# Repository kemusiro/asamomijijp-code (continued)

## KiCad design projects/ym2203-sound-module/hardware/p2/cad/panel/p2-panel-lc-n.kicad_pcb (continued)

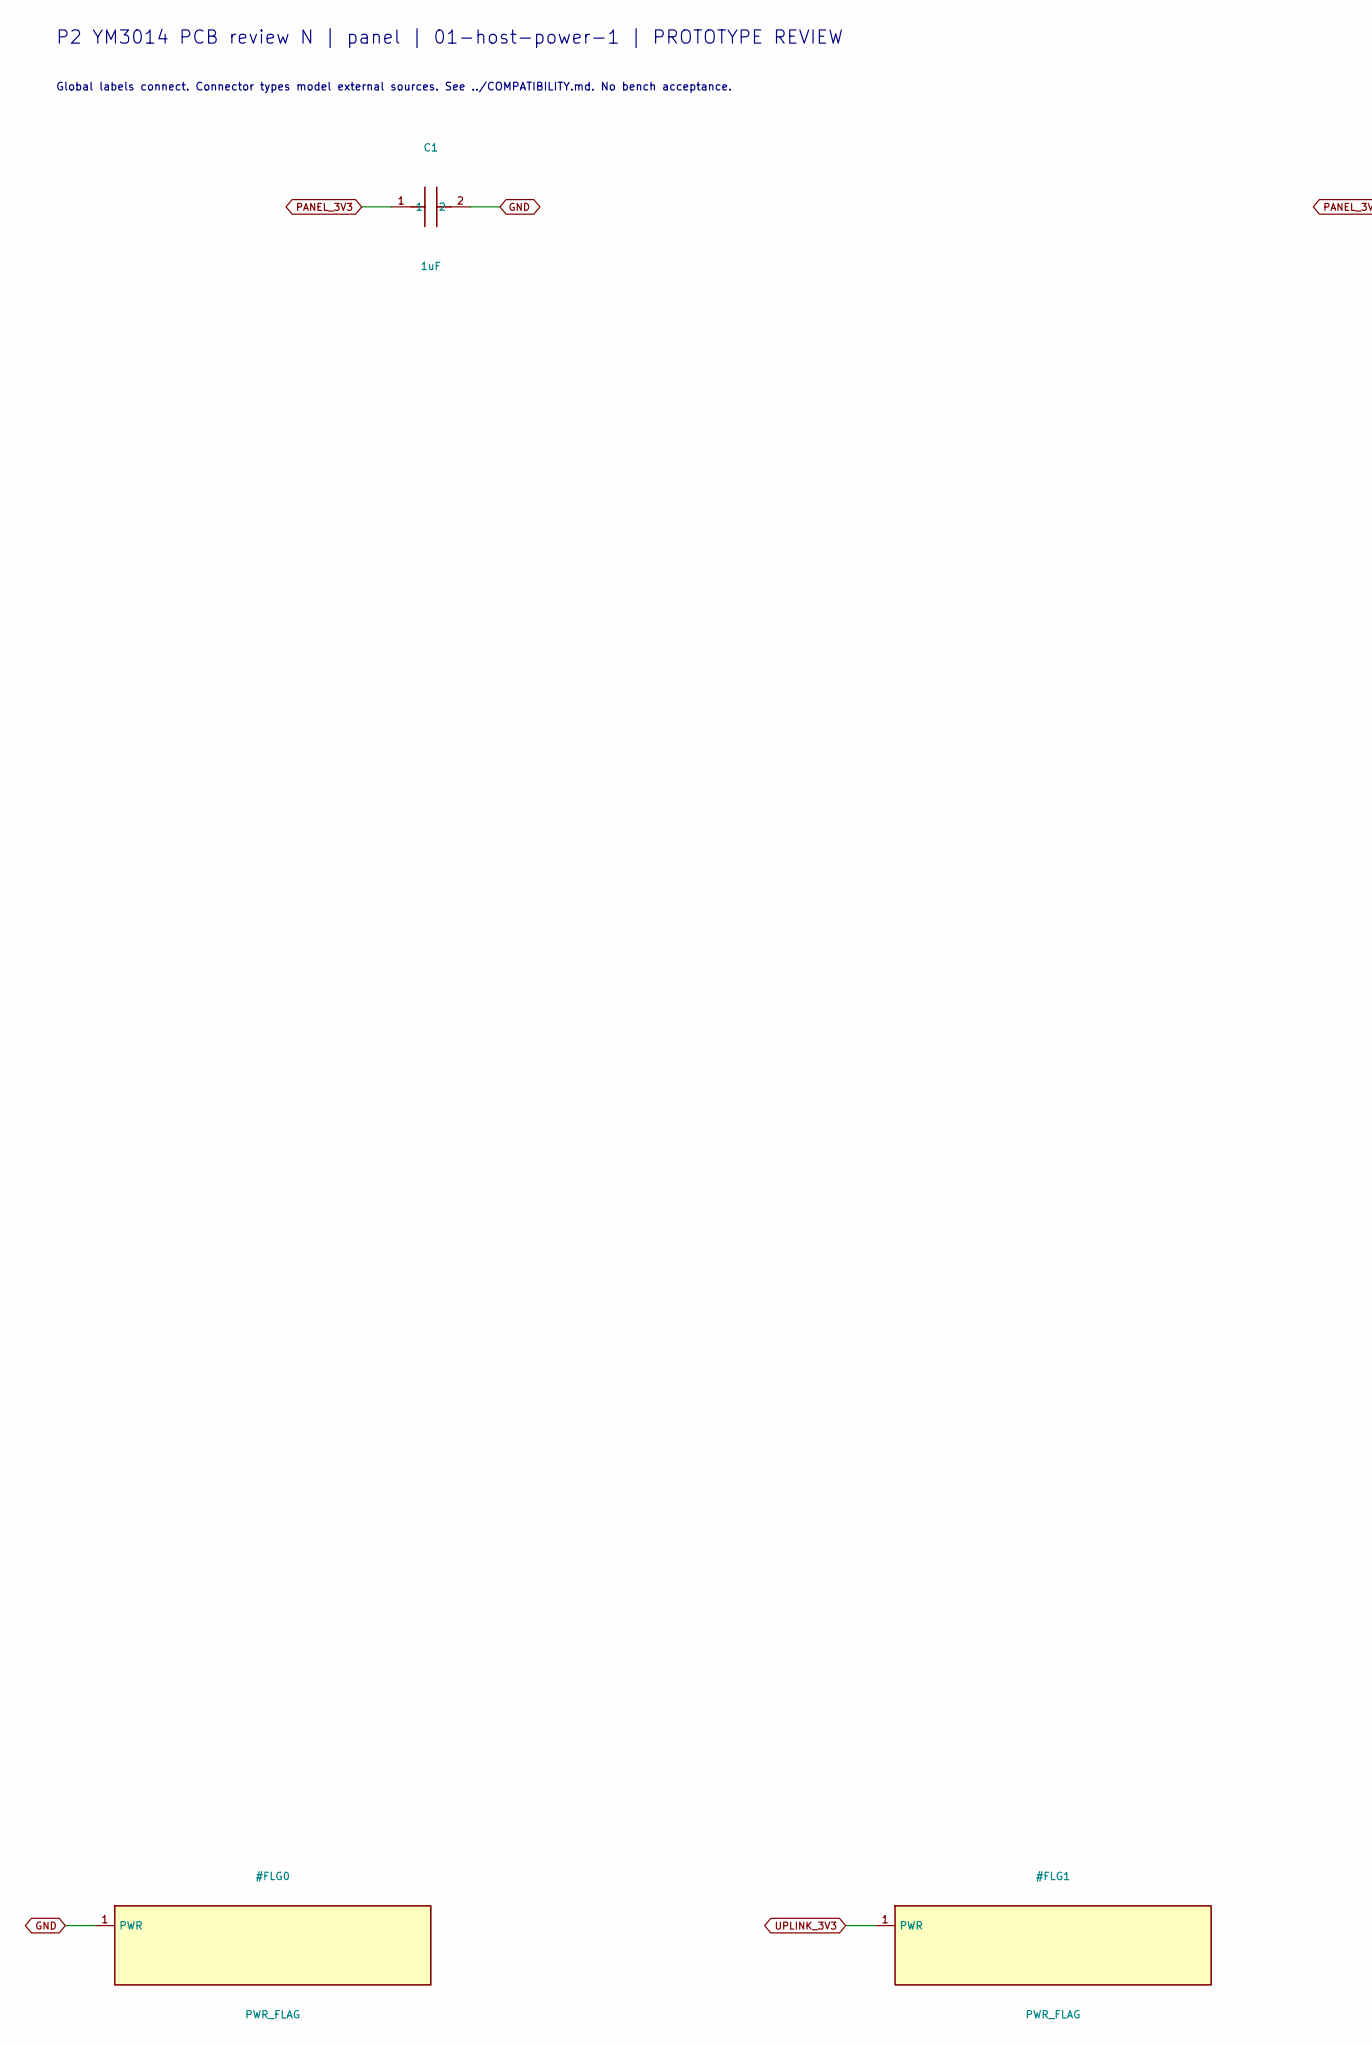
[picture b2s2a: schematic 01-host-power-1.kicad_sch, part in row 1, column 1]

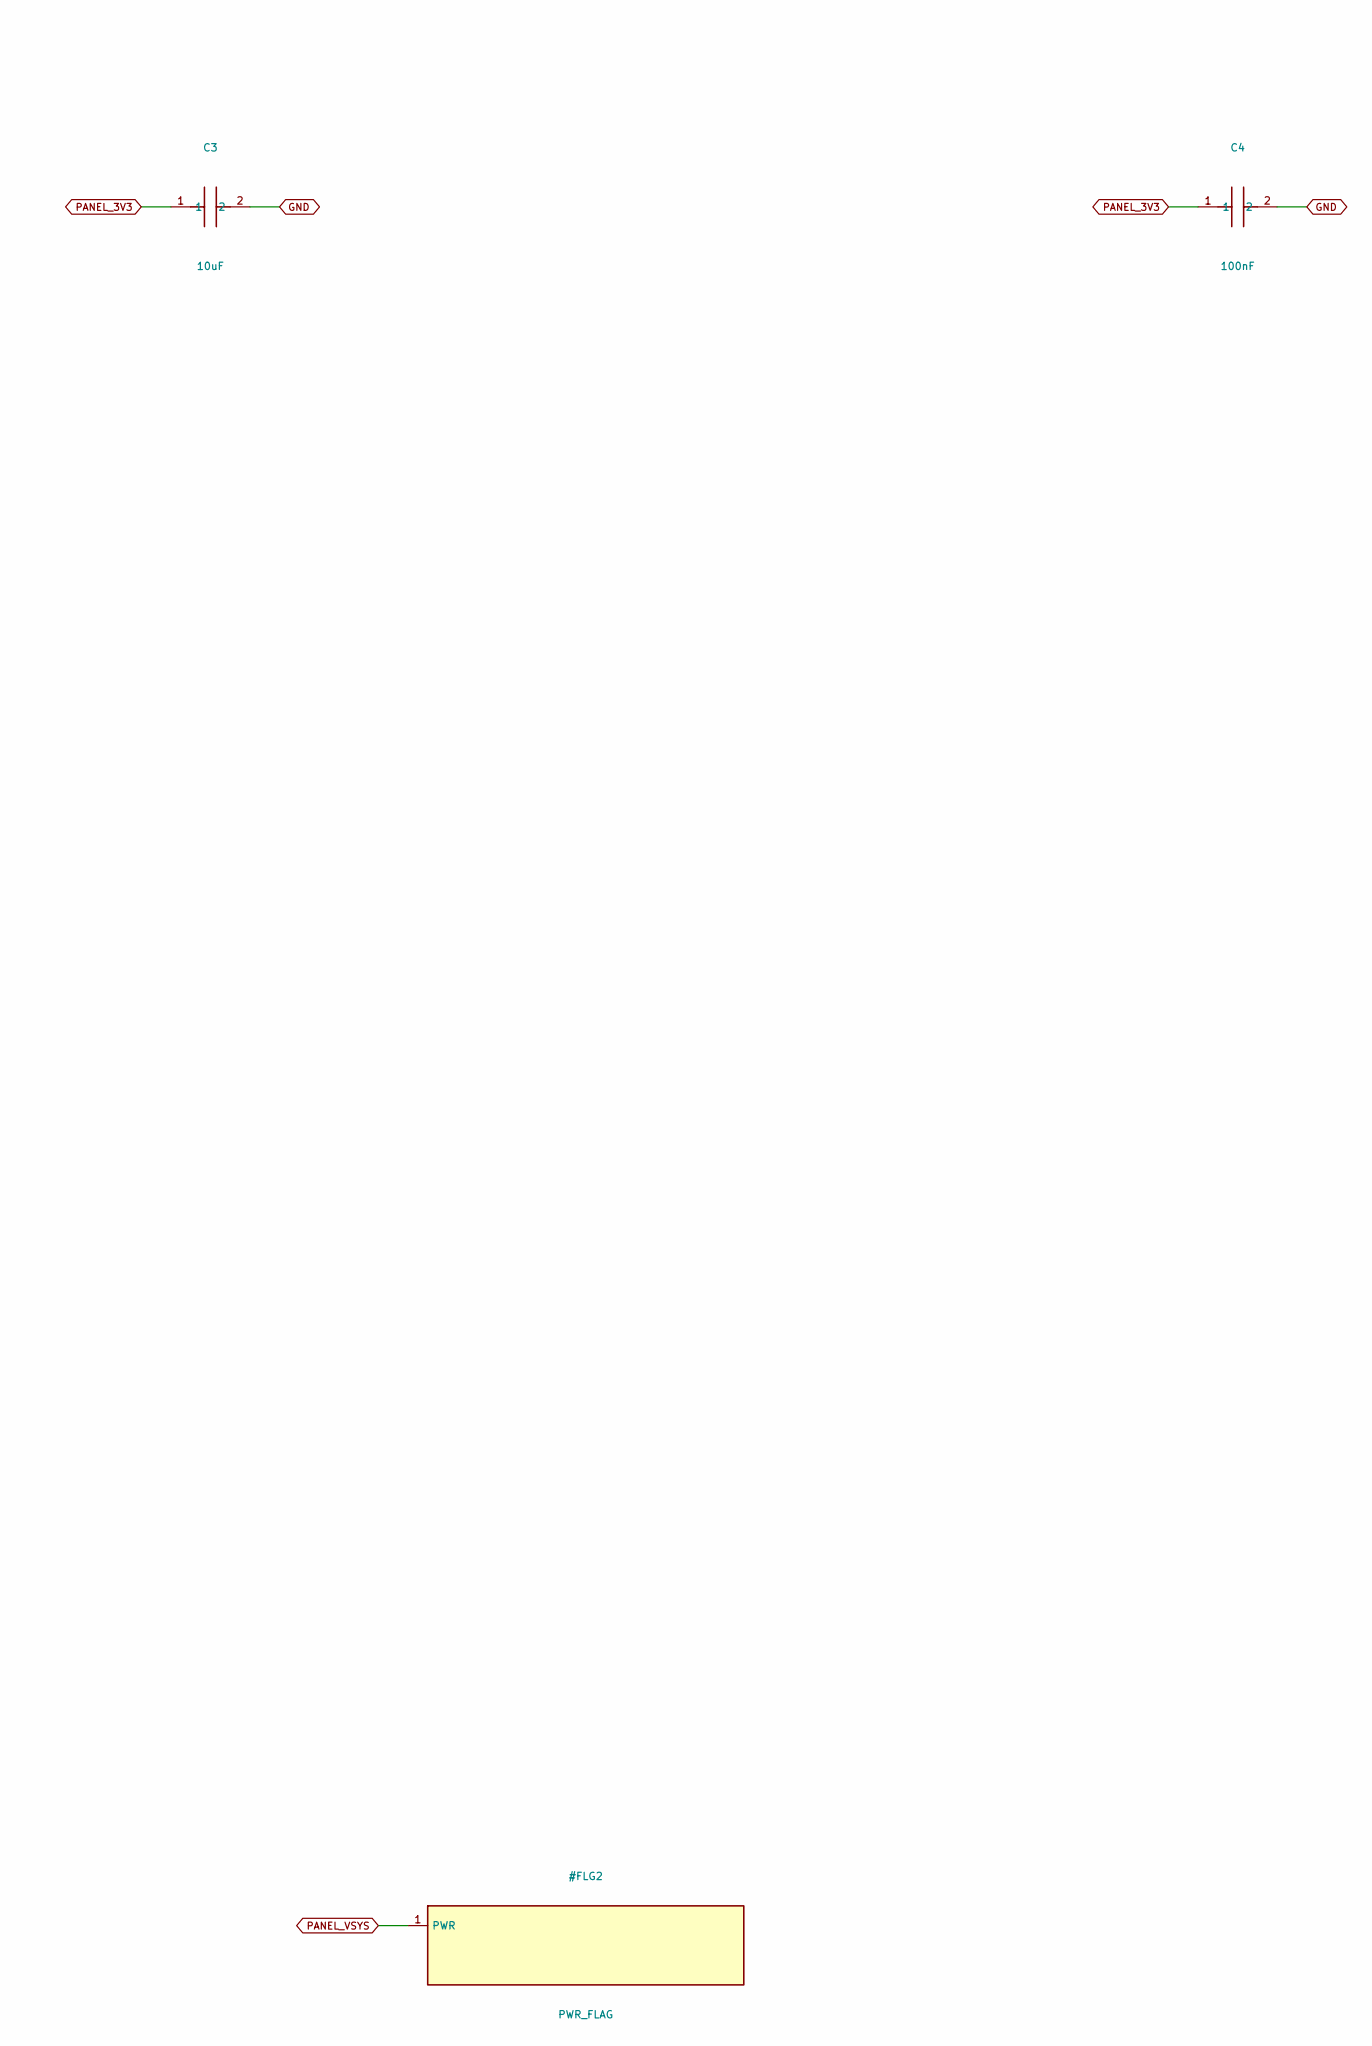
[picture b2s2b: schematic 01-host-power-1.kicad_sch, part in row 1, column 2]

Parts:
C1: 1uF; C_0805_2012Metric
C3: 10uF; C_0805_2012Metric
C4: 100nF; C_0805_2012Metric

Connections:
GND: C1.2, C3.2, C4.2; also elsewhere on the board
PANEL_3V3: C1.1, C3.1, C4.1; also elsewhere on the board

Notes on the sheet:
P2 YM3014 PCB review N | panel | 01-host-power-1 | PROTOTYPE REVIEW
Global labels connect. Connector types model external sources. See ../COMPATIBILITY.md. No bench acceptance.

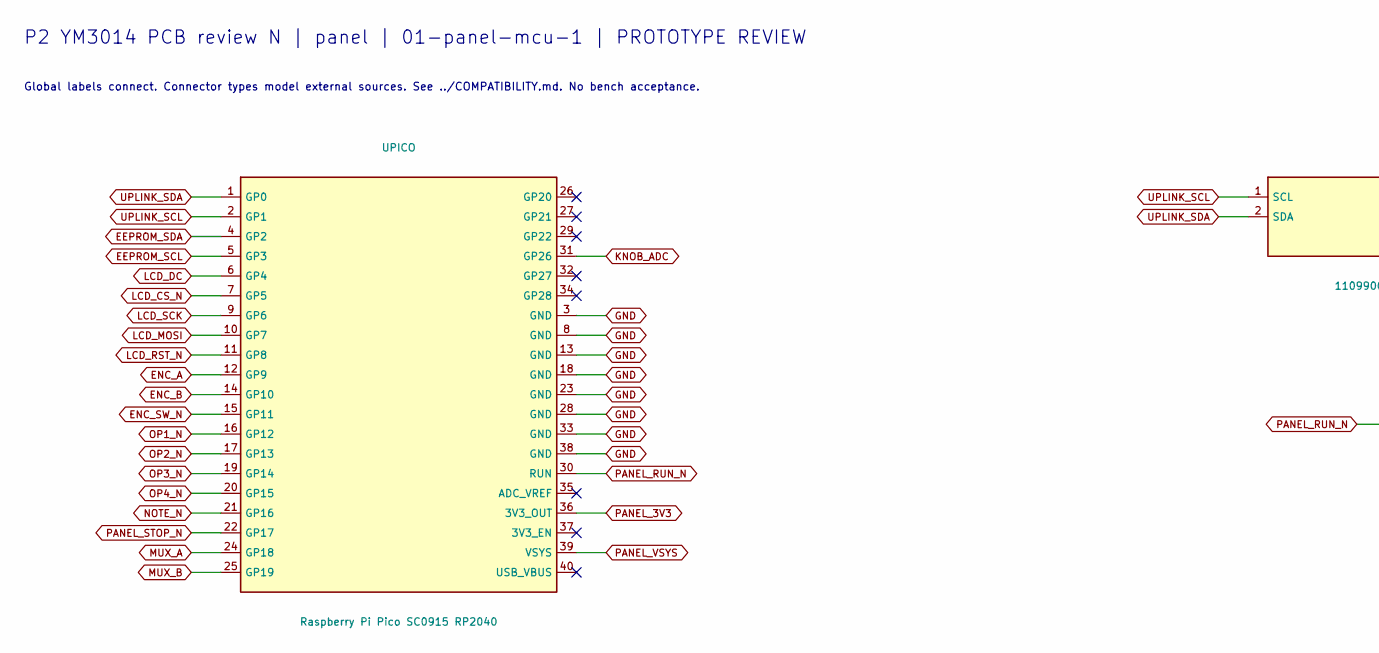
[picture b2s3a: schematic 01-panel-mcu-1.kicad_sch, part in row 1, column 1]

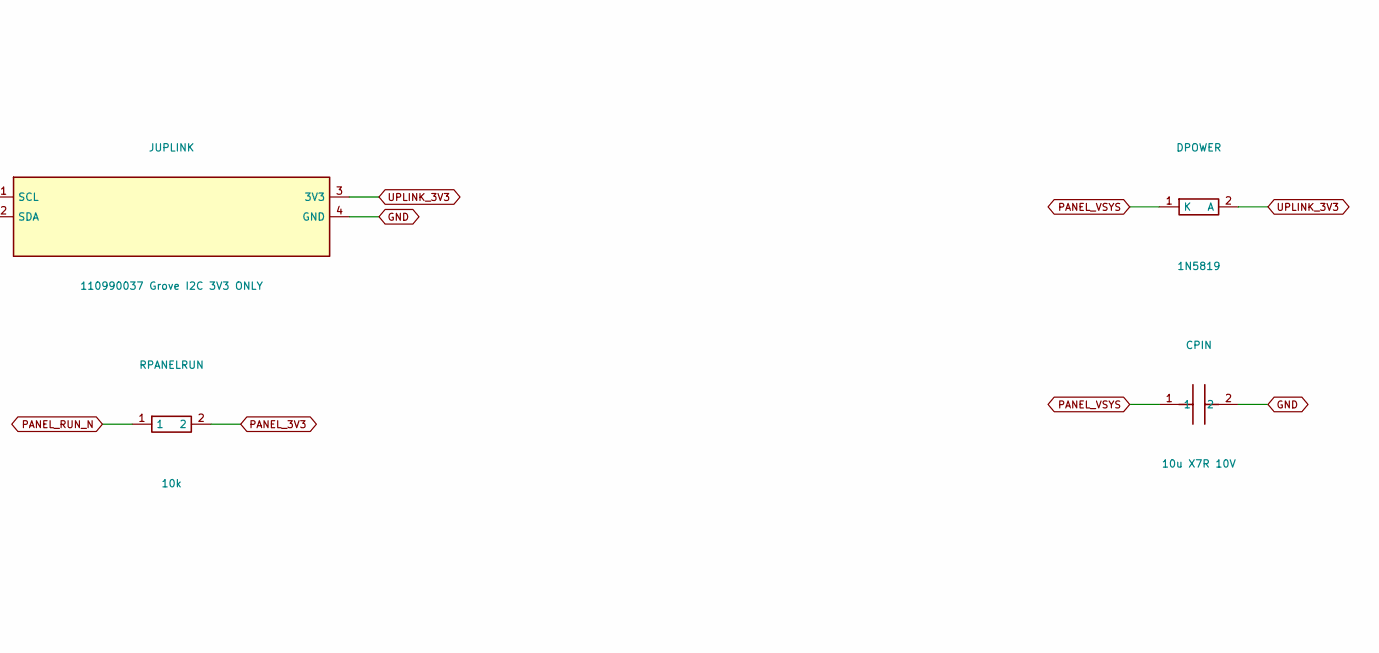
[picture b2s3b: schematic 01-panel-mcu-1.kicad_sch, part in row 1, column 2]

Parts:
CPIN: 10u X7R 10V; C_0805_2012Metric
DPOWER: 1N5819; D_DO-41_SOD81_P10.16mm_Horizontal
JUPLINK: 110990037 Grove I2C 3V3 ONLY; Grove_110990037_RA
RPANELRUN: 10k; R_0805_2012Metric
UPICO: Raspberry Pi Pico SC0915 RP2040; RaspberryPi_Pico_Common_THT

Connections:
EEPROM_SCL: UPICO.5 (GP3); also elsewhere on the board
EEPROM_SDA: UPICO.4 (GP2); also elsewhere on the board
ENC_A: UPICO.12 (GP9); also elsewhere on the board
ENC_B: UPICO.14 (GP10); also elsewhere on the board
ENC_SW_N: UPICO.15 (GP11); also elsewhere on the board
GND: CPIN.2, JUPLINK.4 (GND), UPICO.3 (GND), UPICO.8 (GND), UPICO.13 (GND), UPICO.18 (GND), UPICO.23 (GND), UPICO.28 (GND), UPICO.33 (GND), UPICO.38 (GND); also elsewhere on the board
KNOB_ADC: UPICO.31 (GP26); also elsewhere on the board
LCD_CS_N: UPICO.7 (GP5); also elsewhere on the board
LCD_DC: UPICO.6 (GP4); also elsewhere on the board
LCD_MOSI: UPICO.10 (GP7); also elsewhere on the board
LCD_RST_N: UPICO.11 (GP8); also elsewhere on the board
LCD_SCK: UPICO.9 (GP6); also elsewhere on the board
MUX_A: UPICO.24 (GP18); also elsewhere on the board
MUX_B: UPICO.25 (GP19); also elsewhere on the board
NOTE_N: UPICO.21 (GP16); also elsewhere on the board
OP1_N: UPICO.16 (GP12); also elsewhere on the board
OP2_N: UPICO.17 (GP13); also elsewhere on the board
OP3_N: UPICO.19 (GP14); also elsewhere on the board
OP4_N: UPICO.20 (GP15); also elsewhere on the board
PANEL_3V3: RPANELRUN.2, UPICO.36 (3V3_OUT); also elsewhere on the board
PANEL_RUN_N: RPANELRUN.1, UPICO.30 (RUN)
PANEL_STOP_N: UPICO.22 (GP17); also elsewhere on the board
PANEL_VSYS: CPIN.1, DPOWER.1 (K), UPICO.39 (VSYS)
UPLINK_3V3: DPOWER.2 (A), JUPLINK.3 (3V3)
UPLINK_SCL: JUPLINK.1 (SCL), UPICO.2 (GP1)
UPLINK_SDA: JUPLINK.2 (SDA), UPICO.1 (GP0)

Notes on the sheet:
P2 YM3014 PCB review N | panel | 01-panel-mcu-1 | PROTOTYPE REVIEW
Global labels connect. Connector types model external sources. See ../COMPATIBILITY.md. No bench acceptance.

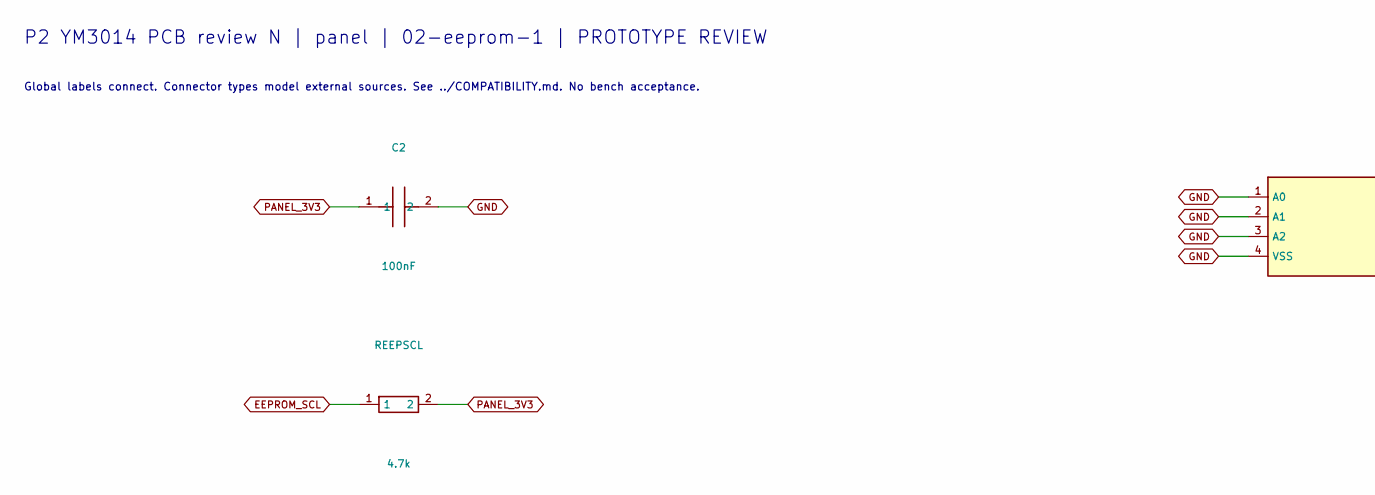
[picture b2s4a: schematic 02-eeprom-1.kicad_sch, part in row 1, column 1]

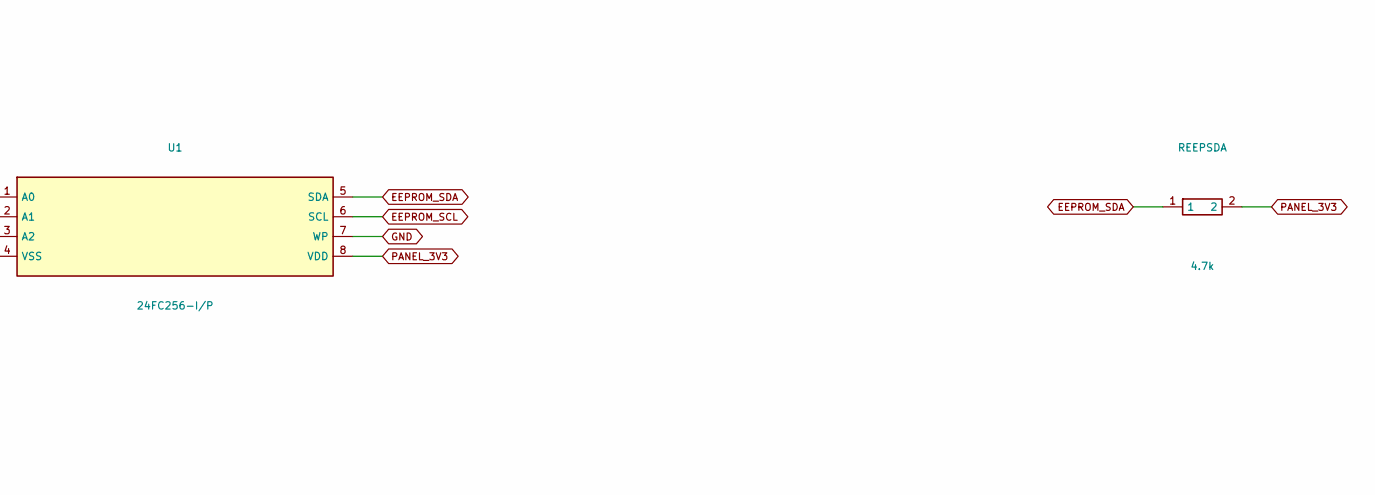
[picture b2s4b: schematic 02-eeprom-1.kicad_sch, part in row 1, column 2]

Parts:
C2: 100nF; C_0805_2012Metric
REEPSCL: 4.7k; R_0805_2012Metric
REEPSDA: 4.7k; R_0805_2012Metric
U1: 24FC256-I/P; DIP-8_W7.62mm

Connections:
EEPROM_SCL: REEPSCL.1, U1.6 (SCL); also elsewhere on the board
EEPROM_SDA: REEPSDA.1, U1.5 (SDA); also elsewhere on the board
GND: C2.2, U1.1 (A0), U1.2 (A1), U1.3 (A2), U1.4 (VSS), U1.7 (WP); also elsewhere on the board
PANEL_3V3: C2.1, REEPSCL.2, REEPSDA.2, U1.8 (VDD); also elsewhere on the board

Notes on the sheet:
P2 YM3014 PCB review N | panel | 02-eeprom-1 | PROTOTYPE REVIEW
Global labels connect. Connector types model external sources. See ../COMPATIBILITY.md. No bench acceptance.

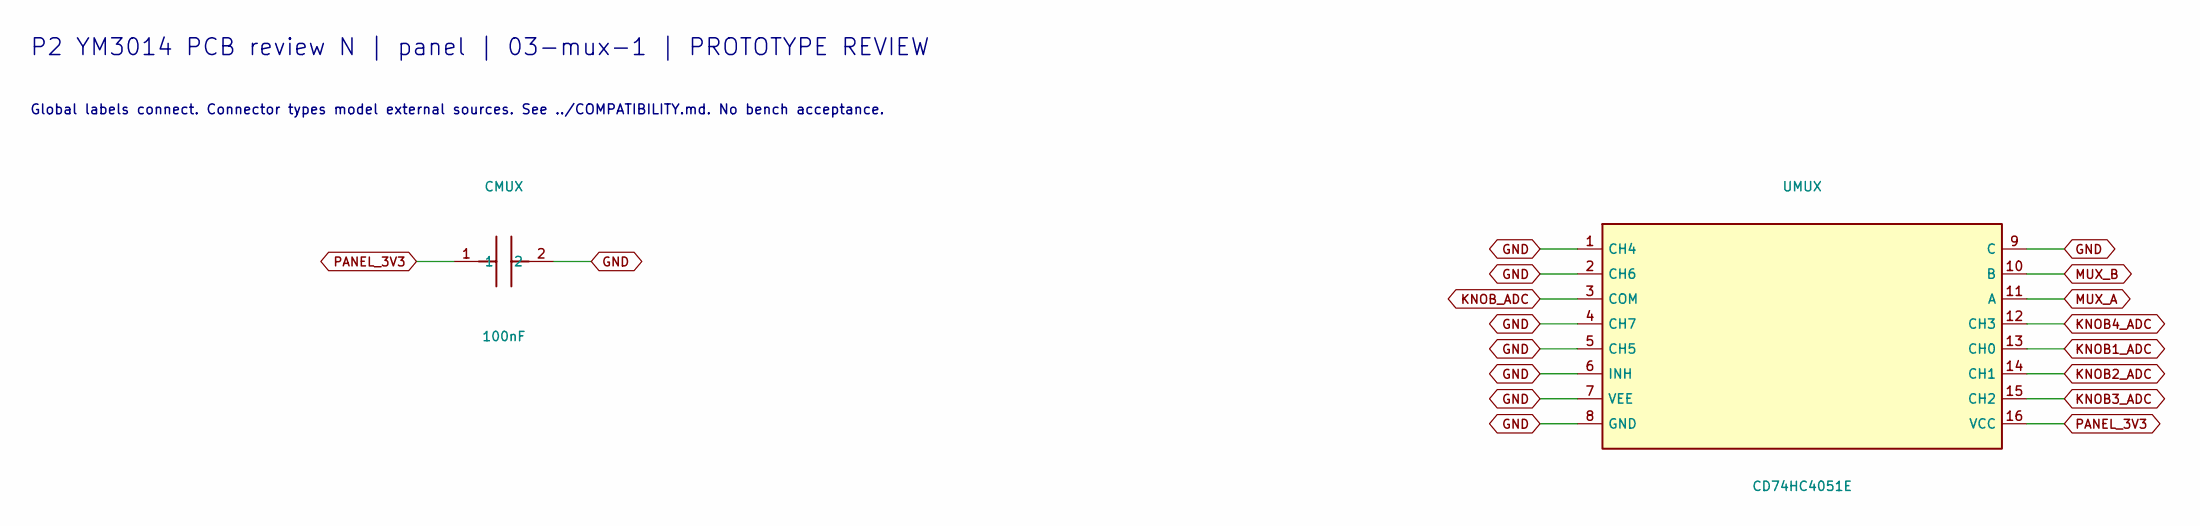
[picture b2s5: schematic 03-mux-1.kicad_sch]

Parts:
CMUX: 100nF; C_0805_2012Metric
UMUX: CD74HC4051E; DIP-16_W7.62mm

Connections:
GND: CMUX.2, UMUX.1 (CH4), UMUX.2 (CH6), UMUX.4 (CH7), UMUX.5 (CH5), UMUX.6 (INH), UMUX.7 (VEE), UMUX.8 (GND), UMUX.9 (C); also elsewhere on the board
KNOB1_ADC: UMUX.13 (CH0); also elsewhere on the board
KNOB2_ADC: UMUX.14 (CH1); also elsewhere on the board
KNOB3_ADC: UMUX.15 (CH2); also elsewhere on the board
KNOB4_ADC: UMUX.12 (CH3); also elsewhere on the board
KNOB_ADC: UMUX.3 (COM); also elsewhere on the board
MUX_A: UMUX.11 (A); also elsewhere on the board
MUX_B: UMUX.10 (B); also elsewhere on the board
PANEL_3V3: CMUX.1, UMUX.16 (VCC); also elsewhere on the board

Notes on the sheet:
P2 YM3014 PCB review N | panel | 03-mux-1 | PROTOTYPE REVIEW
Global labels connect. Connector types model external sources. See ../COMPATIBILITY.md. No bench acceptance.

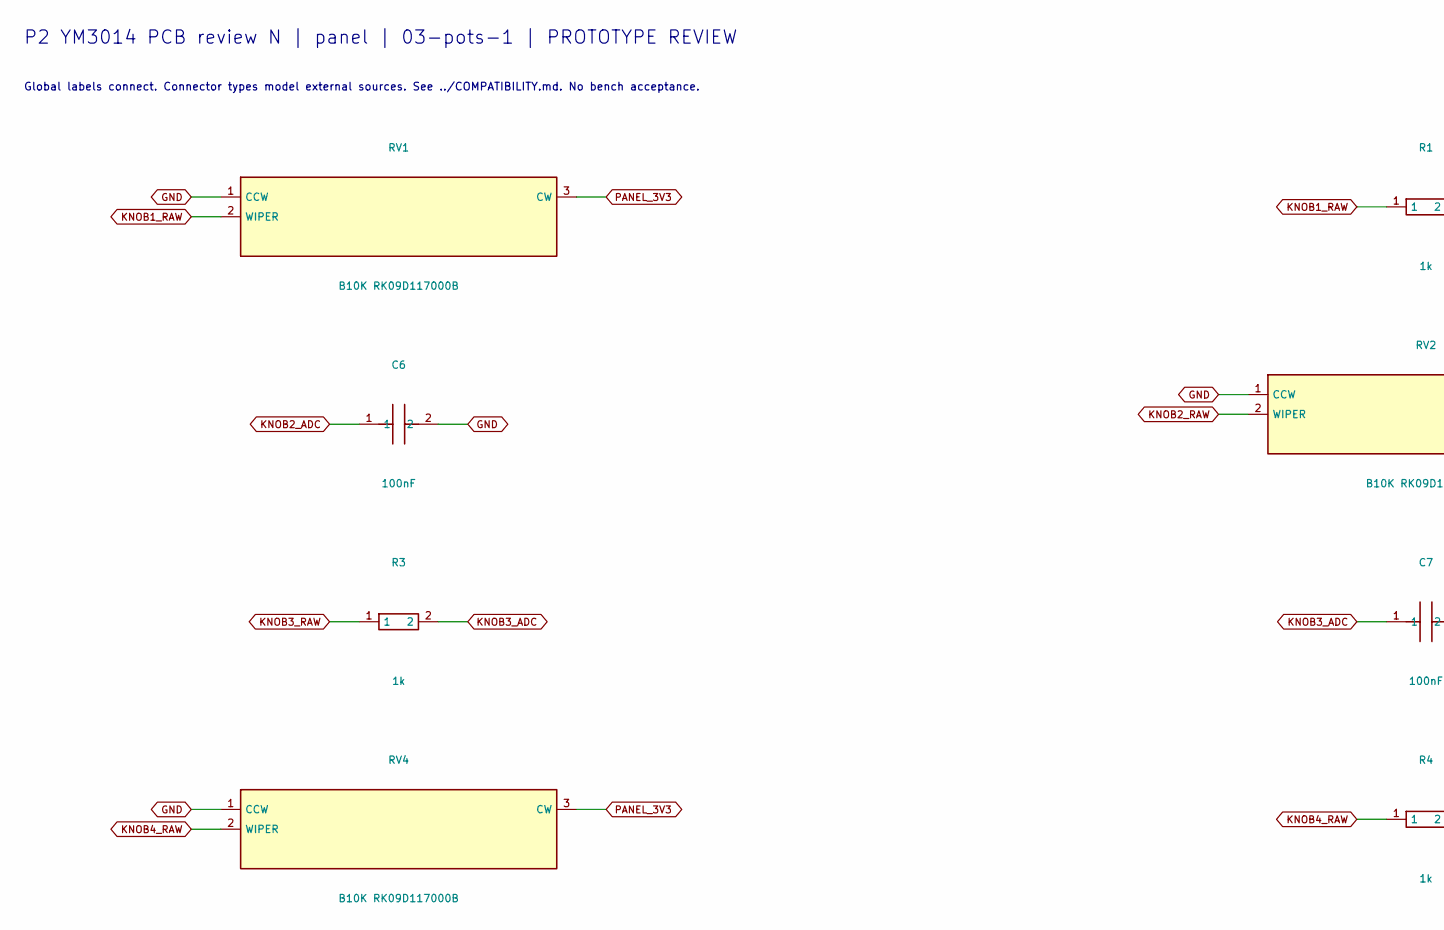
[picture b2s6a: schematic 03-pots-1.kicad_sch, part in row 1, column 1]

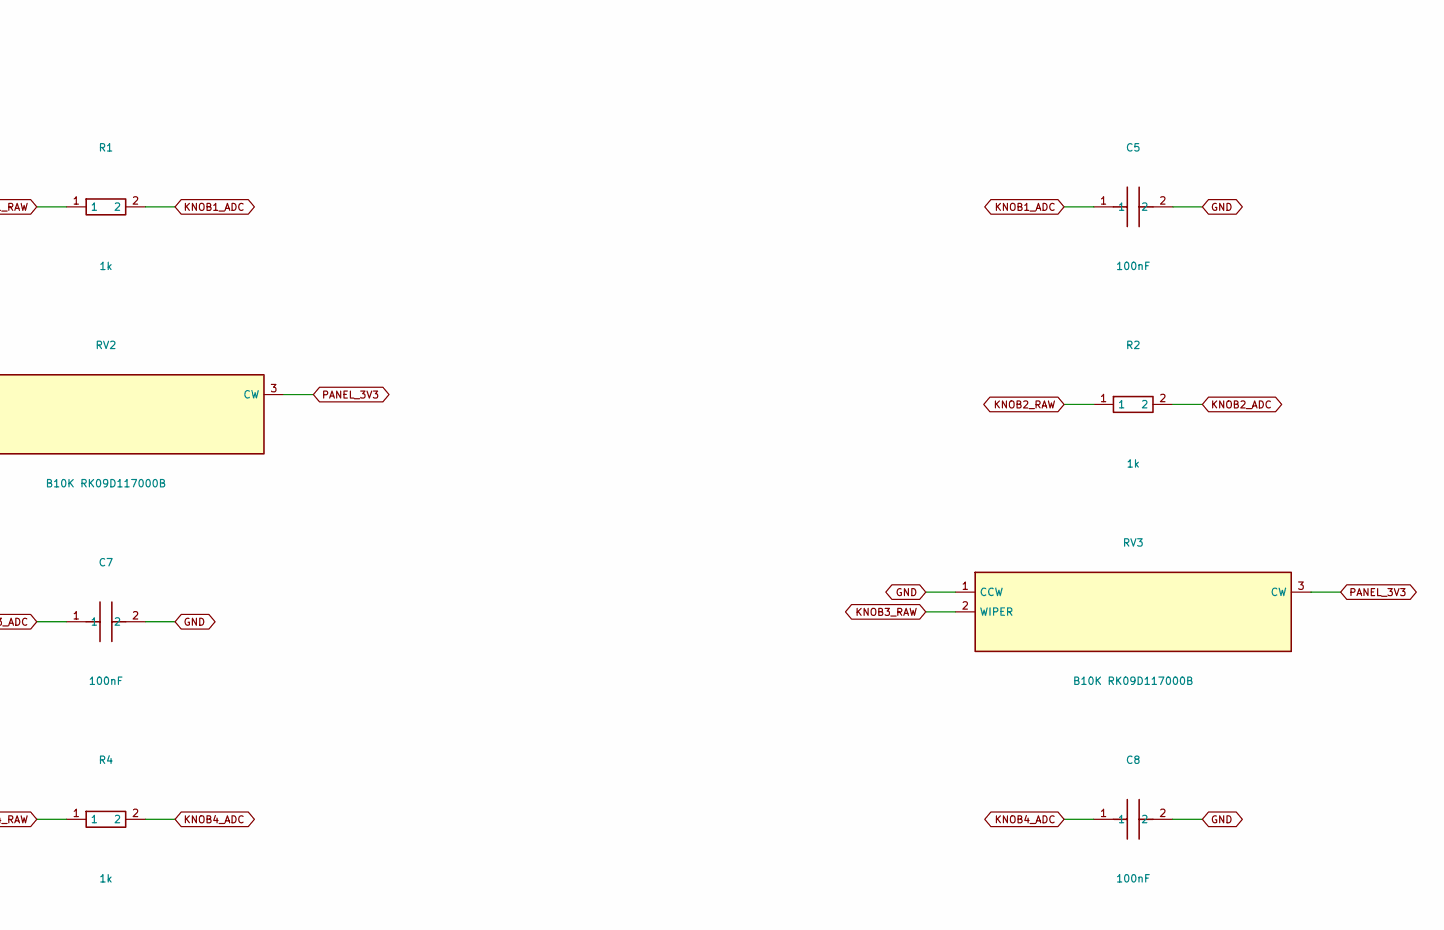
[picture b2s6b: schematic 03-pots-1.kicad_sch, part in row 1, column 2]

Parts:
C5, C6, C7, C8: 100nF; C_0805_2012Metric
R1, R2, R3, R4: 1k; R_0805_2012Metric
RV1, RV2, RV3, RV4: B10K RK09D117000B; Potentiometer_Alps_RK09K_Single_Vertical

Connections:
GND: C5.2, C6.2, C7.2, C8.2, RV1.1 (CCW), RV2.1 (CCW), RV3.1 (CCW), RV4.1 (CCW); also elsewhere on the board
KNOB1_ADC: C5.1, R1.2; also elsewhere on the board
KNOB1_RAW: R1.1, RV1.2 (WIPER)
KNOB2_ADC: C6.1, R2.2; also elsewhere on the board
KNOB2_RAW: R2.1, RV2.2 (WIPER)
KNOB3_ADC: C7.1, R3.2; also elsewhere on the board
KNOB3_RAW: R3.1, RV3.2 (WIPER)
KNOB4_ADC: C8.1, R4.2; also elsewhere on the board
KNOB4_RAW: R4.1, RV4.2 (WIPER)
PANEL_3V3: RV1.3 (CW), RV2.3 (CW), RV3.3 (CW), RV4.3 (CW); also elsewhere on the board

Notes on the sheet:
P2 YM3014 PCB review N | panel | 03-pots-1 | PROTOTYPE REVIEW
Global labels connect. Connector types model external sources. See ../COMPATIBILITY.md. No bench acceptance.

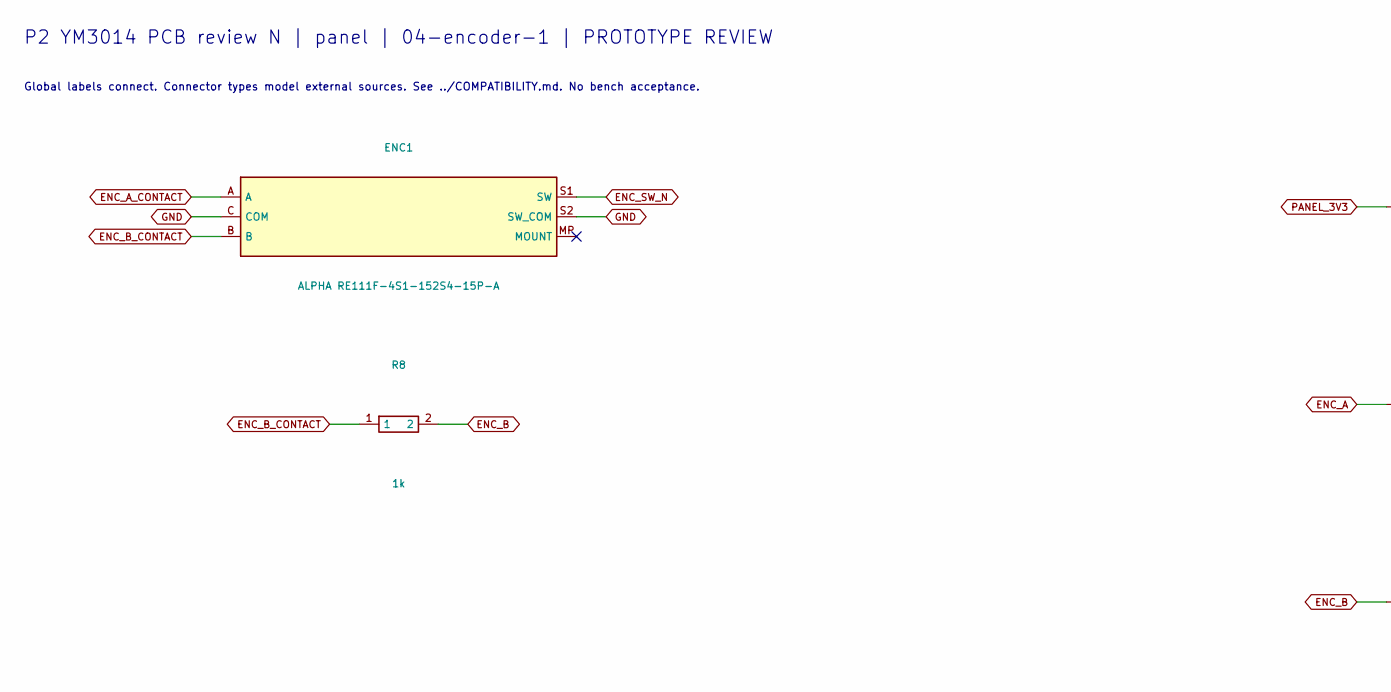
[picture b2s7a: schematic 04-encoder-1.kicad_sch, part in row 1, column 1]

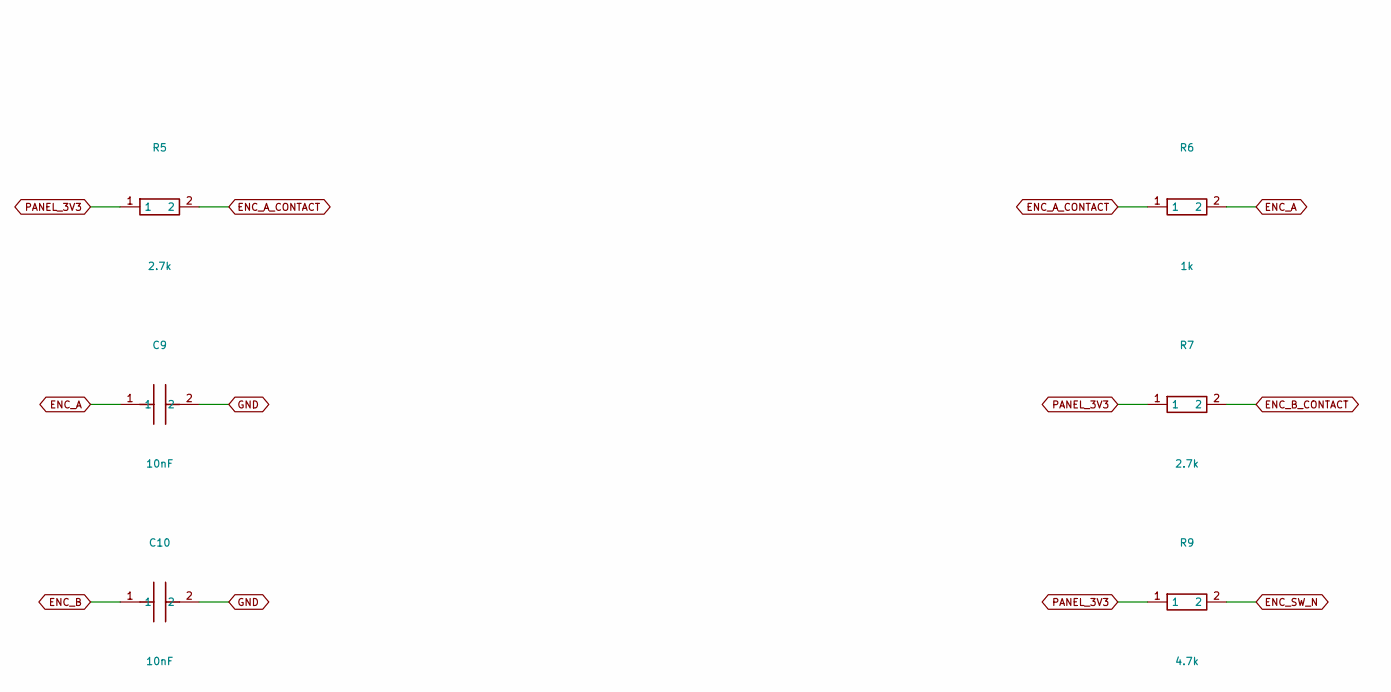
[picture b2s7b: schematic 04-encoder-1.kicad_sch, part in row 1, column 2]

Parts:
C9, C10: 10nF; C_0805_2012Metric
ENC1: ALPHA RE111F-4S1-152S4-15P-A; RE111F_4S1_ReviewB
R5, R7: 2.7k; R_0805_2012Metric
R6, R8: 1k; R_0805_2012Metric
R9: 4.7k; R_0805_2012Metric

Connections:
ENC_A: C9.1, R6.2; also elsewhere on the board
ENC_A_CONTACT: ENC1.A, R5.2, R6.1
ENC_B: C10.1, R8.2; also elsewhere on the board
ENC_B_CONTACT: ENC1.B, R7.2, R8.1
ENC_SW_N: ENC1.S1 (SW), R9.2; also elsewhere on the board
GND: C9.2, C10.2, ENC1.C (COM), ENC1.S2 (SW_COM); also elsewhere on the board
PANEL_3V3: R5.1, R7.1, R9.1; also elsewhere on the board

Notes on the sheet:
P2 YM3014 PCB review N | panel | 04-encoder-1 | PROTOTYPE REVIEW
Global labels connect. Connector types model external sources. See ../COMPATIBILITY.md. No bench acceptance.

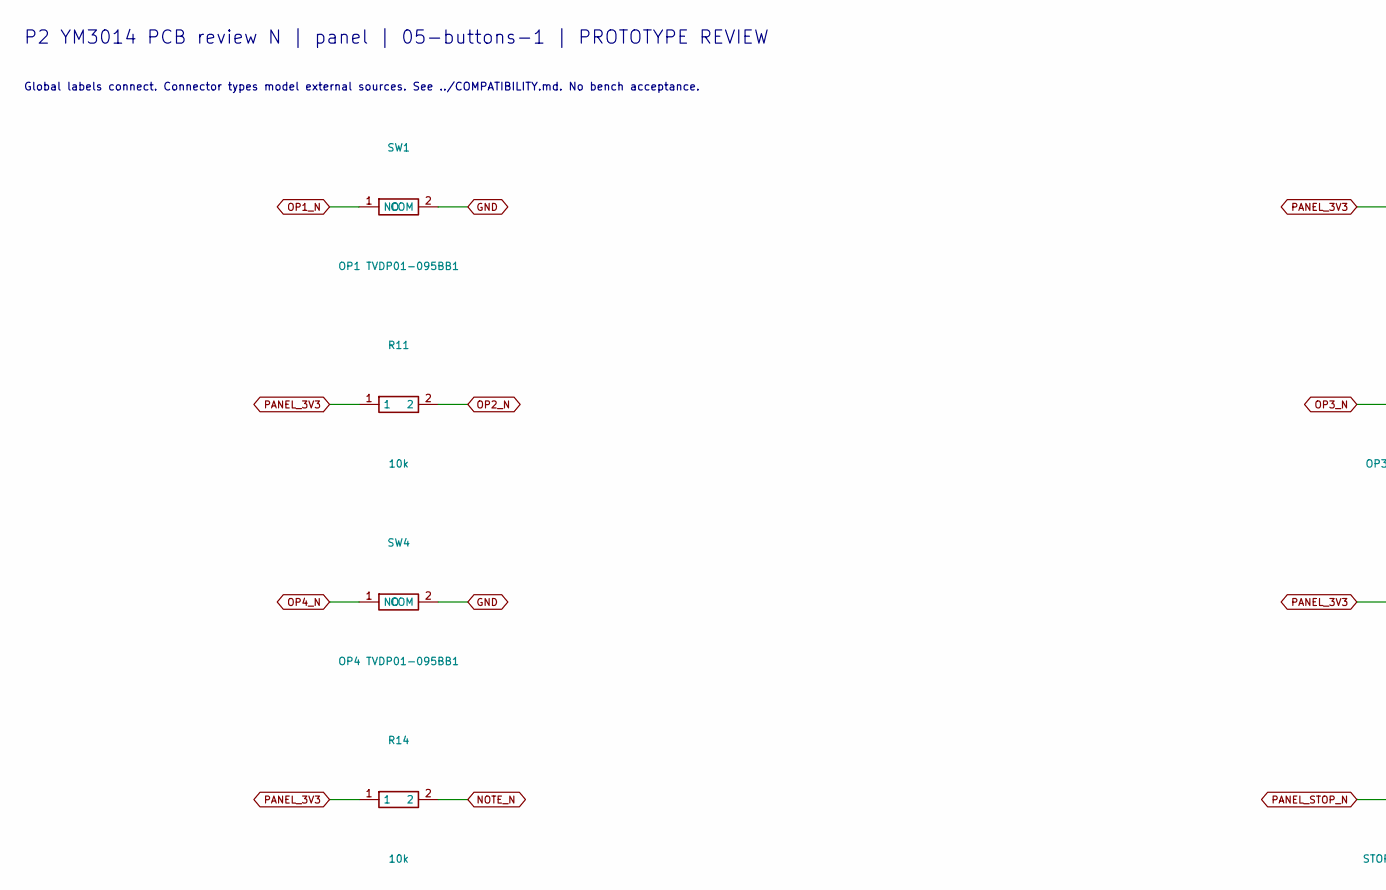
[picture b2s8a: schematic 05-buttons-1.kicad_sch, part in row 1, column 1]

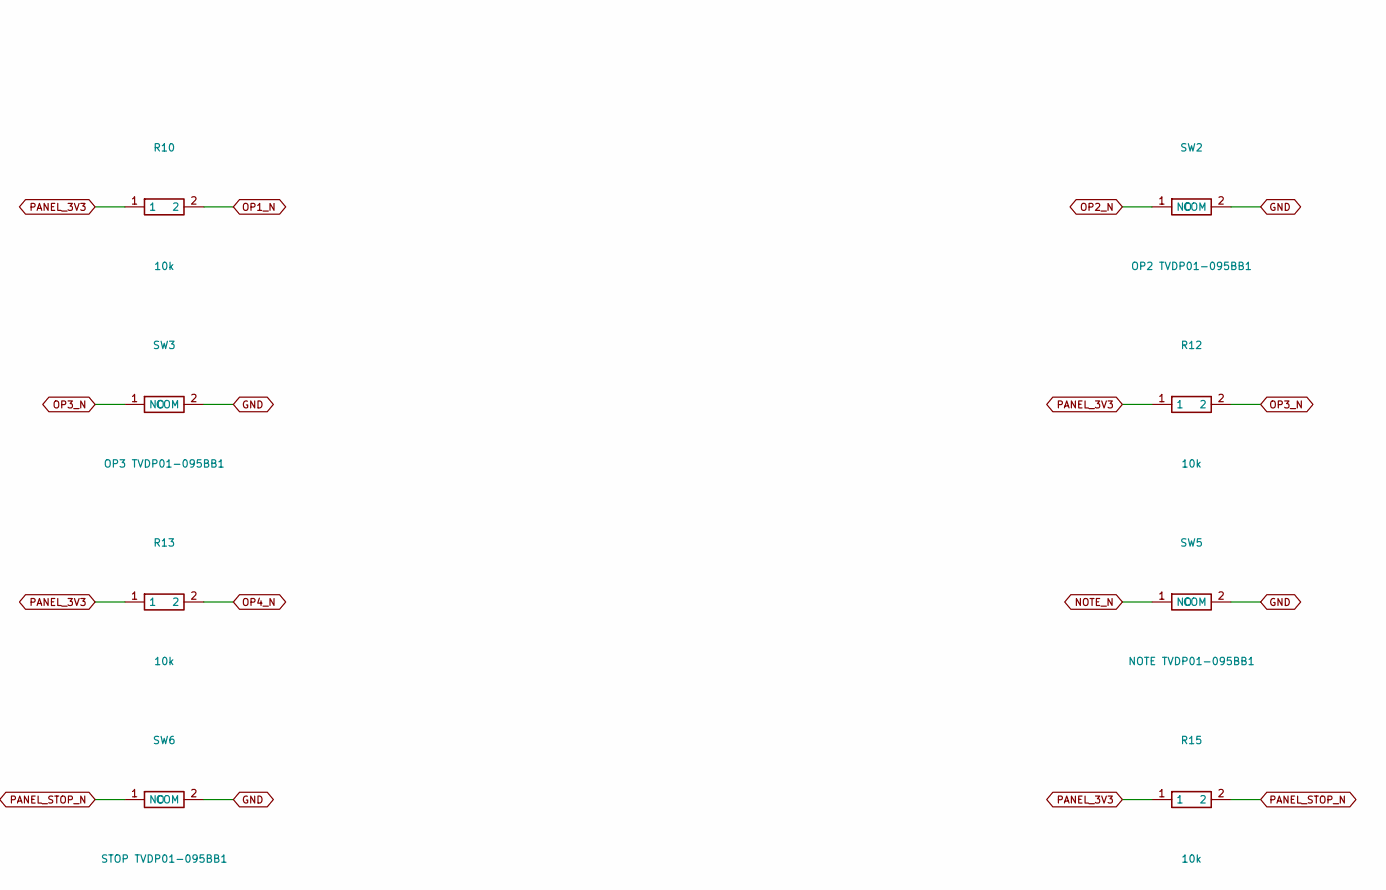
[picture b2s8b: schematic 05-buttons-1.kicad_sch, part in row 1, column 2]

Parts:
R10, R11, R12, R13, R14, R15: 10k; R_0805_2012Metric
SW1: OP1 TVDP01-095BB1; SW_PUSH_6mm_H9.5mm
SW2: OP2 TVDP01-095BB1; SW_PUSH_6mm_H9.5mm
SW3: OP3 TVDP01-095BB1; SW_PUSH_6mm_H9.5mm
SW4: OP4 TVDP01-095BB1; SW_PUSH_6mm_H9.5mm
SW5: NOTE TVDP01-095BB1; SW_PUSH_6mm_H9.5mm
SW6: STOP TVDP01-095BB1; SW_PUSH_6mm_H9.5mm

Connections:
GND: SW1.2 (COM), SW2.2 (COM), SW3.2 (COM), SW4.2 (COM), SW5.2 (COM), SW6.2 (COM); also elsewhere on the board
NOTE_N: R14.2, SW5.1 (NO); also elsewhere on the board
OP1_N: R10.2, SW1.1 (NO); also elsewhere on the board
OP2_N: R11.2, SW2.1 (NO); also elsewhere on the board
OP3_N: R12.2, SW3.1 (NO); also elsewhere on the board
OP4_N: R13.2, SW4.1 (NO); also elsewhere on the board
PANEL_3V3: R10.1, R11.1, R12.1, R13.1, R14.1, R15.1; also elsewhere on the board
PANEL_STOP_N: R15.2, SW6.1 (NO); also elsewhere on the board

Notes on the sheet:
P2 YM3014 PCB review N | panel | 05-buttons-1 | PROTOTYPE REVIEW
Global labels connect. Connector types model external sources. See ../COMPATIBILITY.md. No bench acceptance.

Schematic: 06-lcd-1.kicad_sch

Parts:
J5: M154 LCD direct 1x8 socket / no harness; LCD_M154_Socket_1x08
R16, R17: 10k; R_0805_2012Metric
R18, R19: 33; R_0805_2012Metric

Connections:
GND: J5.1 (GND); also elsewhere on the board
LCD_CLK_OUT: J5.3 (SCL_SPI), R18.2
LCD_CS_N: J5.7 (CS), R16.2; also elsewhere on the board
LCD_DC: J5.6 (DC); also elsewhere on the board
LCD_DIN_OUT: J5.4 (SDA_SPI), R19.2
LCD_MOSI: R19.1; also elsewhere on the board
LCD_RST_N: J5.5 (RES), R17.2; also elsewhere on the board
LCD_SCK: R18.1; also elsewhere on the board
PANEL_3V3: J5.2 (VCC), J5.8 (BLK), R16.1, R17.1; also elsewhere on the board

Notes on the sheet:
P2 YM3014 PCB review N | panel | 06-lcd-1 | PROTOTYPE REVIEW
Global labels connect. Connector types model external sources. See ../COMPATIBILITY.md. No bench acceptance.
